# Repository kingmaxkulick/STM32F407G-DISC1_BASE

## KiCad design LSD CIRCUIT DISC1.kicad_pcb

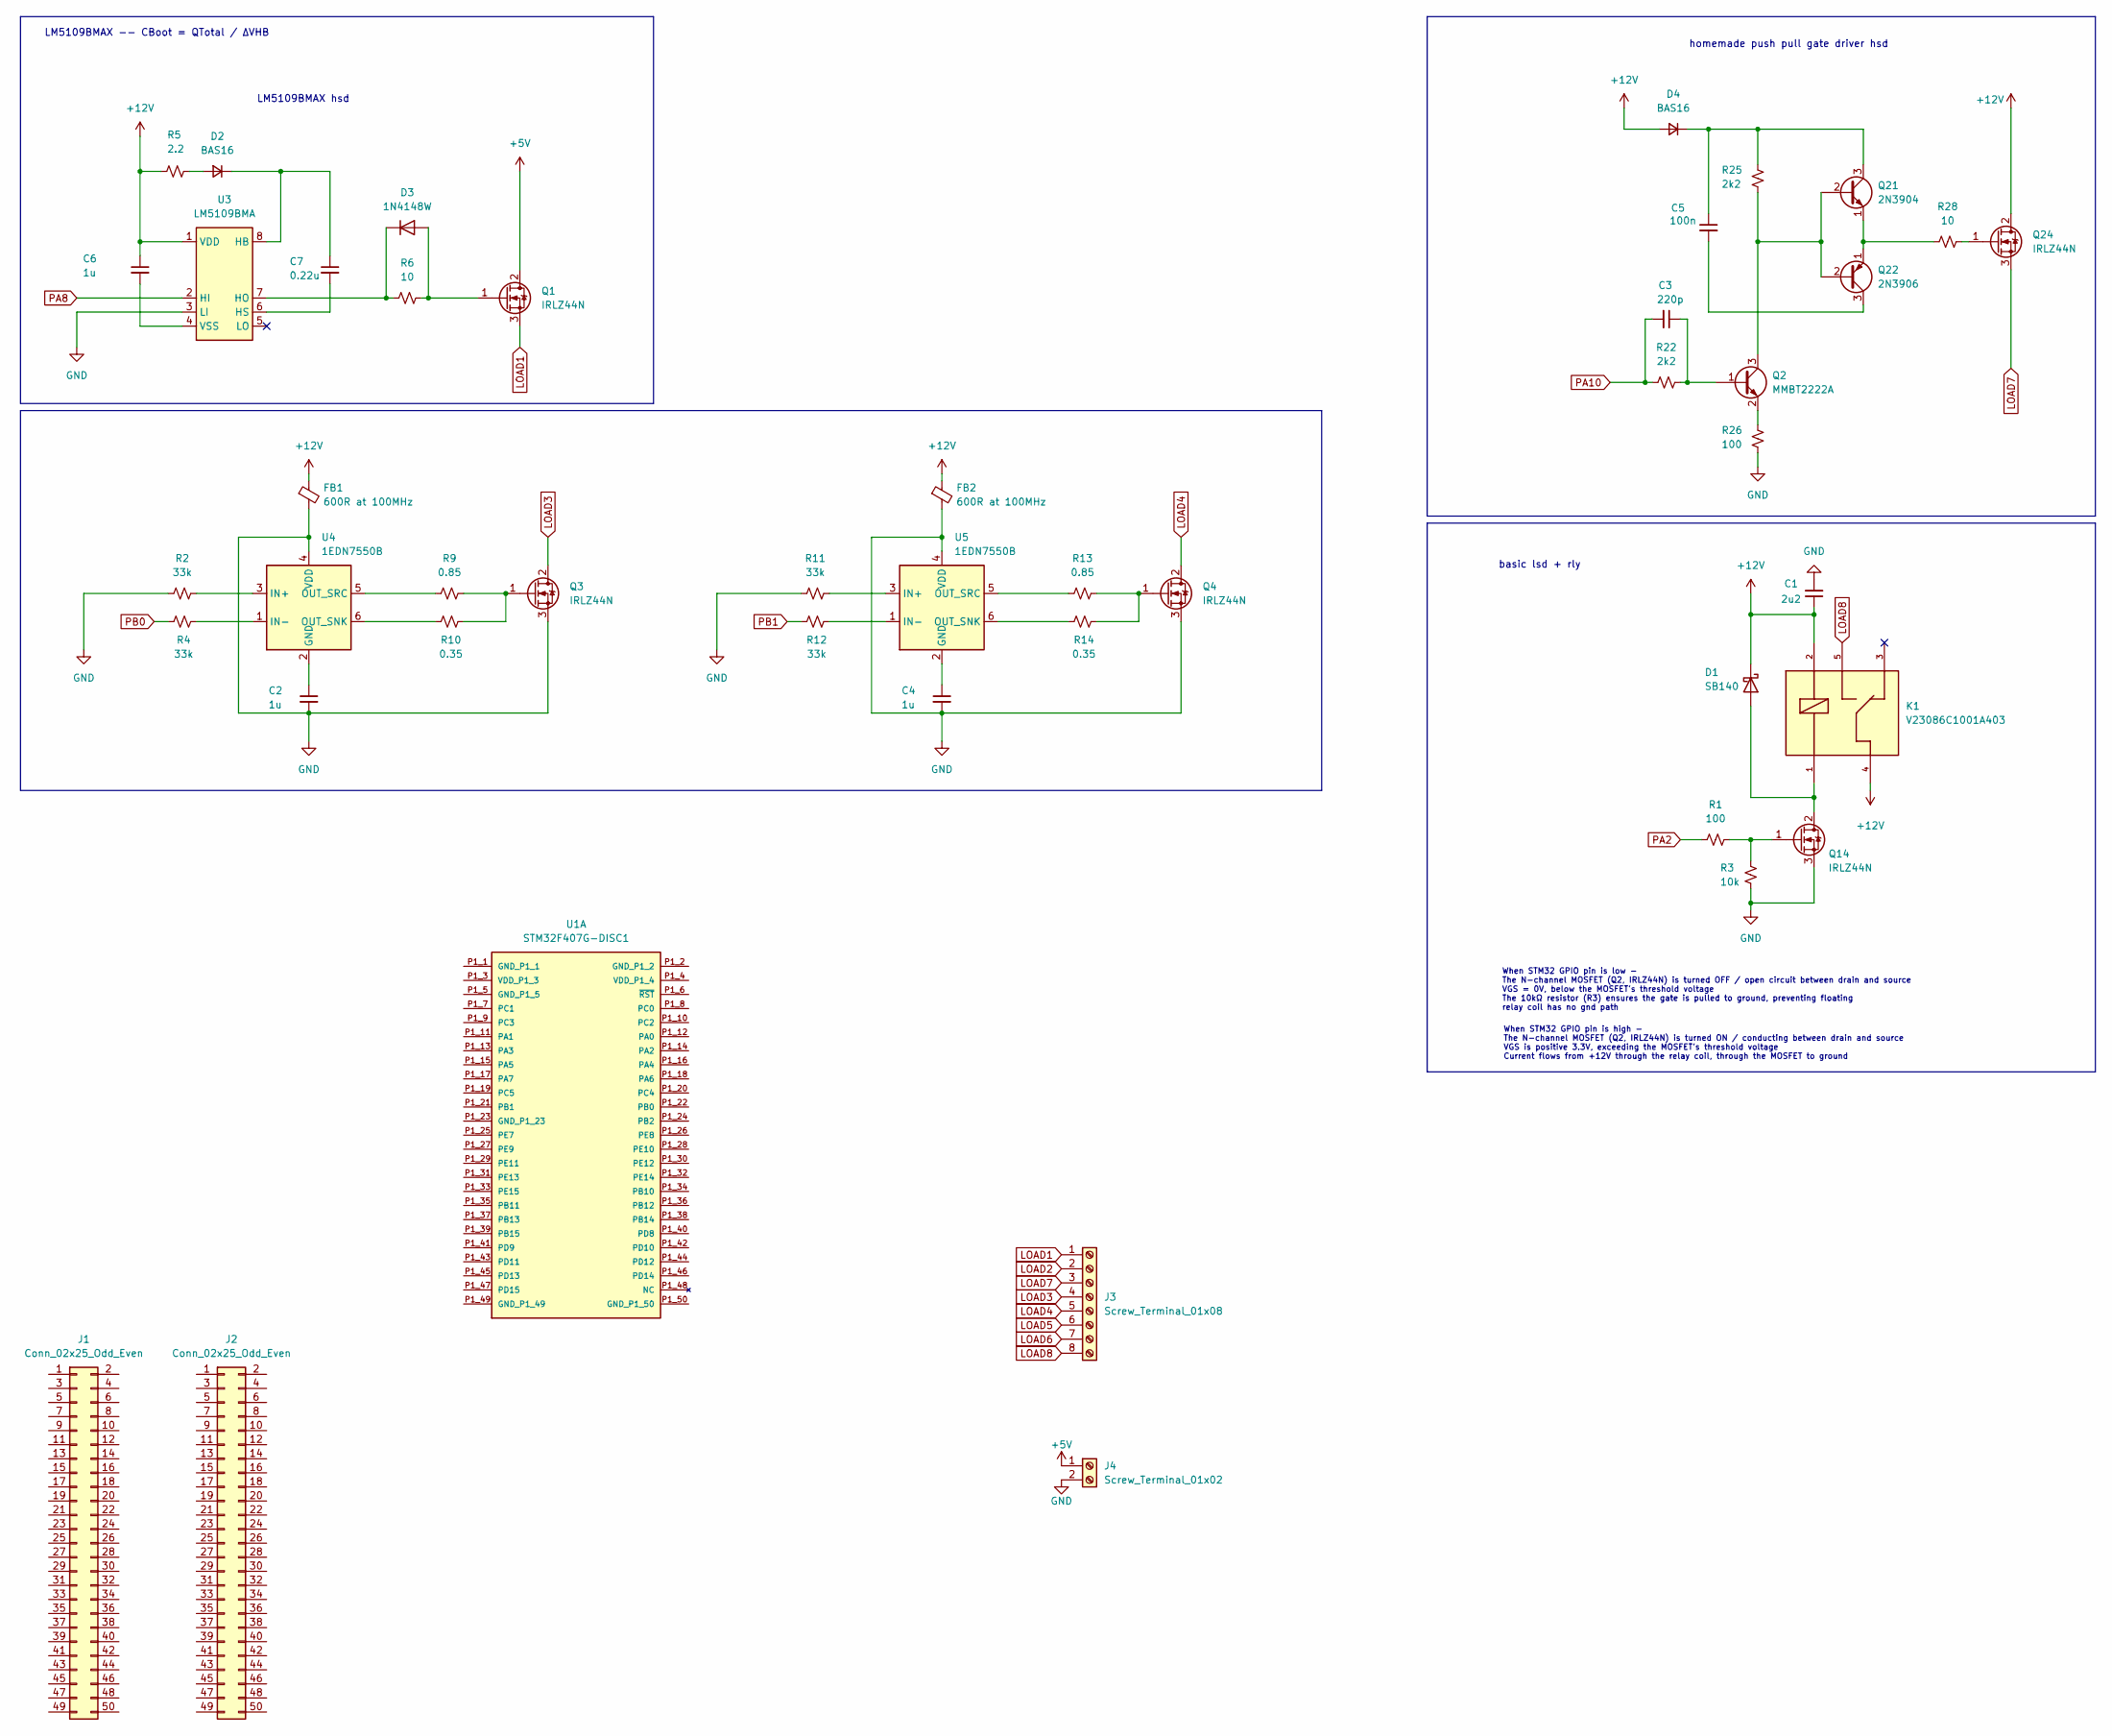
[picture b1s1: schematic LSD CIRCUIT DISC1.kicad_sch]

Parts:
C1: 2u2; C_1206_3216Metric; LCSC Part # C13585
C2, C4: 1u; C_0603_1608Metric
C3: 220p; C_1206_3216Metric; LCSC Part # C13585
C5: 100n; C_1206_3216Metric; LCSC Part # C13585
C6: 1u; C_1206_3216Metric
C7: 0.22u; C_1206_3216Metric
D1: SB140; D_DO-41_SOD81_P10.16mm_Horizontal
D2, D4: BAS16; SOT-23
D3: 1N4148W; D_SOD-123
FB1, FB2: 600R at 100MHz; L_0805_2012Metric
J1, J2: Conn_02x25_Odd_Even; PinSocket_2x25_P2.54mm_Vertical_SMD
J3: Screw_Terminal_01x08; TerminalBlock_Phoenix_PT-1,5-8-3.5-H_1x08_P3.50mm_Horizontal
J4: Screw_Terminal_01x02; TerminalBlock_Phoenix_PT-1,5-2-3.5-H_1x02_P3.50mm_Horizontal
K1: V23086C1001A403
Q1, Q3, Q4, Q14, Q24: IRLZ44N; TO-220-3_Vertical
Q2: MMBT2222A; SOT-23
Q21: 2N3904; TO-92_Inline
Q22: 2N3906; TO-92_Inline
R1, R26: 100; R_0603_1608Metric
R2, R4, R11, R12: 33k; R_0603_1608Metric
R3: 10k; R_0603_1608Metric
R5: 2.2; R_0603_1608Metric
R6, R28: 10; R_0603_1608Metric
R9, R13: 0.85; R_0603_1608Metric
R10, R14: 0.35; R_0603_1608Metric
R22, R25: 2k2; R_0603_1608Metric
U1: STM32F407G-DISC1; MODULE_STM32F407G-DISC1; PARTREV 7
U3: LM5109BMA; SOIC-8_3.9x4.9mm_P1.27mm
U4, U5: 1EDN7550B; SOT-23-6

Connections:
+5V: J4.1, Q1.2 (D)
+12V: C1.1, C6.1, D1.1 (K), D4.2 (A), FB1.1, FB2.1, K1.2, K1.4, Q24.2 (D), R5.1, U3.1 (VDD)
GND: C1.2, C2.2, C4.2, FB1.2, FB2.2, J4.2, Q3.3 (S), Q4.3 (S), Q14.3 (S), R2.2, R3.2, R11.2, R26.1, U3.3 (LI), U4.4 (VDD), U5.4 (VDD)
LOAD1: J3.1, Q1.3 (S)
LOAD2: J3.2
LOAD3: J3.4, Q3.2 (D)
LOAD4: J3.5, Q4.2 (D)
LOAD5: J3.6
LOAD6: J3.7
LOAD7: J3.3, Q24.3 (S)
LOAD8: J3.8, K1.5
unnamed: D1.2 (A), K1.1, Q14.2 (D)
unnamed: D2.2 (A), R5.2
unnamed: C7.1, D2.1 (K), U3.8 (HB)
unnamed: D3.2 (A), Q1.1 (G), R6.1
unnamed: D3.1 (K), R6.2, U3.7 (HO)
unnamed: C5.1, D4.1 (K), Q21.3 (C), R25.2
unnamed: C3.1, Q2.1 (B), R22.2
unnamed: Q2.3 (C), Q21.2 (B), Q22.2 (B), R25.1
unnamed: Q2.2 (E), R26.2
unnamed: Q3.1 (G), R9.1, R10.1
unnamed: Q4.1 (G), R13.1, R14.1
unnamed: Q14.1 (G), R1.2, R3.1
unnamed: Q21.1 (E), Q22.1 (E), R28.2
unnamed: C5.2, Q22.3 (C)
unnamed: Q24.1 (G), R28.1
unnamed: C7.2, U3.6 (HS)
unnamed: C6.2, U3.4 (VSS)
unnamed: C2.1, U4.2 (GND)
unnamed: R2.1, U4.3 (IN+)
unnamed: R4.1, U4.1 (IN-)
unnamed: R10.2, U4.6 (OUT_SNK)
unnamed: R9.2, U4.5 (OUT_SRC)
unnamed: C4.1, U5.2 (GND)
unnamed: R11.1, U5.3 (IN+)
unnamed: R12.1, U5.1 (IN-)
unnamed: R14.2, U5.6 (OUT_SNK)
unnamed: R13.2, U5.5 (OUT_SRC)
PA2: R1.1
PA8: U3.2 (HI)
PA10: C3.2, R22.1
PB0: R4.2
PB1: R12.2

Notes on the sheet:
basic lsd + rly
LM5109BMAX -- CBoot = QTotal / ΔVHB
homemade push pull gate driver hsd
LM5109BMAX hsd
When STM32 GPIO pin is low - The N-channel MOSFET (Q2, IRLZ44N) is turned OFF / open circuit between drain and source VGS = 0V, below the MOSFET's threshold voltage The 10kΩ resistor (R3) ensures the gate is pulled to ground, preventing floating relay coil has no gnd path
When STM32 GPIO pin is high - The N-channel MOSFET (Q2, IRLZ44N) is turned ON / conducting between drain and source VGS is positive 3.3V, exceeding the MOSFET's threshold voltage Current flows from +12V through the relay coil, through the MOSFET to ground

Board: 2 copper layers, 46 parts (0 on the bottom side), 36 nets, no tracks yet.
